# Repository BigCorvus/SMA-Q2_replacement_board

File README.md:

# SMA-Q2_replacement_board

Custom replacement board with an nrf52840 module based on the feather board. It features a https://abracon.com/realtimeclock/AB-RTCMC-32.768kHz-IBO5-S3.pdf RTC with a tiny superca for timekeeping. It will take care of generating the extcomin signal and minute-wise updates of the display. In between the updates the MCU can be turned off completely which can lead to very low  overall power consumption of the watch. That way one can just write Sketches for the nrf52840 without having to engineer low power stuff, so one should have a reliable device capable for everyday use. You have native USB for DFU und other communication via the charging cable which has a USB plug connected to the  four contacts anyway. The accelerometer is a BMA400 and the heart rate sensor based on https://pulsesensor.com sitting on a custom flex PCB connected to an analog input: https://github.com/BigCorvus/PulseSensor-for-SMA-Q2/tree/master

The current version snapfits almost perfectly into the LCD frame. Had to file a corner for a fraction of a millimeter.

The BOM is not quite finished yet because I have not setteled on the final component values, but most of them should be straightforward. Just consult the schematc. 
The dual P-Channel mosfets might be CMLDM8005 TR PBFREE (Digikey 1514-CMLDM8005TRPBFREECT-ND). 
Pushbuttons are LS12T2-T (Digikey 1642-1312-1-ND).
The supercap is Seiko CPH3225A (728-1127-1-ND). 
The RTC is Abracon AB-RTCMC-32.768kHz-IBO5-S3 (535-13301-1-ND). 
The display connectors are 255-3056-1-ND and 255-5667-ND. 
Accelerometer is 828-1081-1-ND (BMA400). 
Schottky diodes are 497-7163-1-ND. 
Flash chip is 1970-1011-1-ND. 
LDO is 296-24059-1-ND. 
The BT module is a Raytac MDBT50Q (1597-1678-ND). 
Watch crystal: 478-5428-1-ND. 
Mosfet for vibrator is DMG1012UW-7DICT-ND.
LED for HR sensor: 1497-1162-1-ND, Opamp: MCP6001T-I/LTCT-ND.
The vibration motor is 8mm in diameter and 2mm high. Can be found on Aliexpress.  
  
Newer version: https://github.com/BigCorvus/SMA-Q2_replacement_board_v2  
Arduino Firmware: https://github.com/BigCorvus/SMA-Q2-nrf52840-dualMode-firmware

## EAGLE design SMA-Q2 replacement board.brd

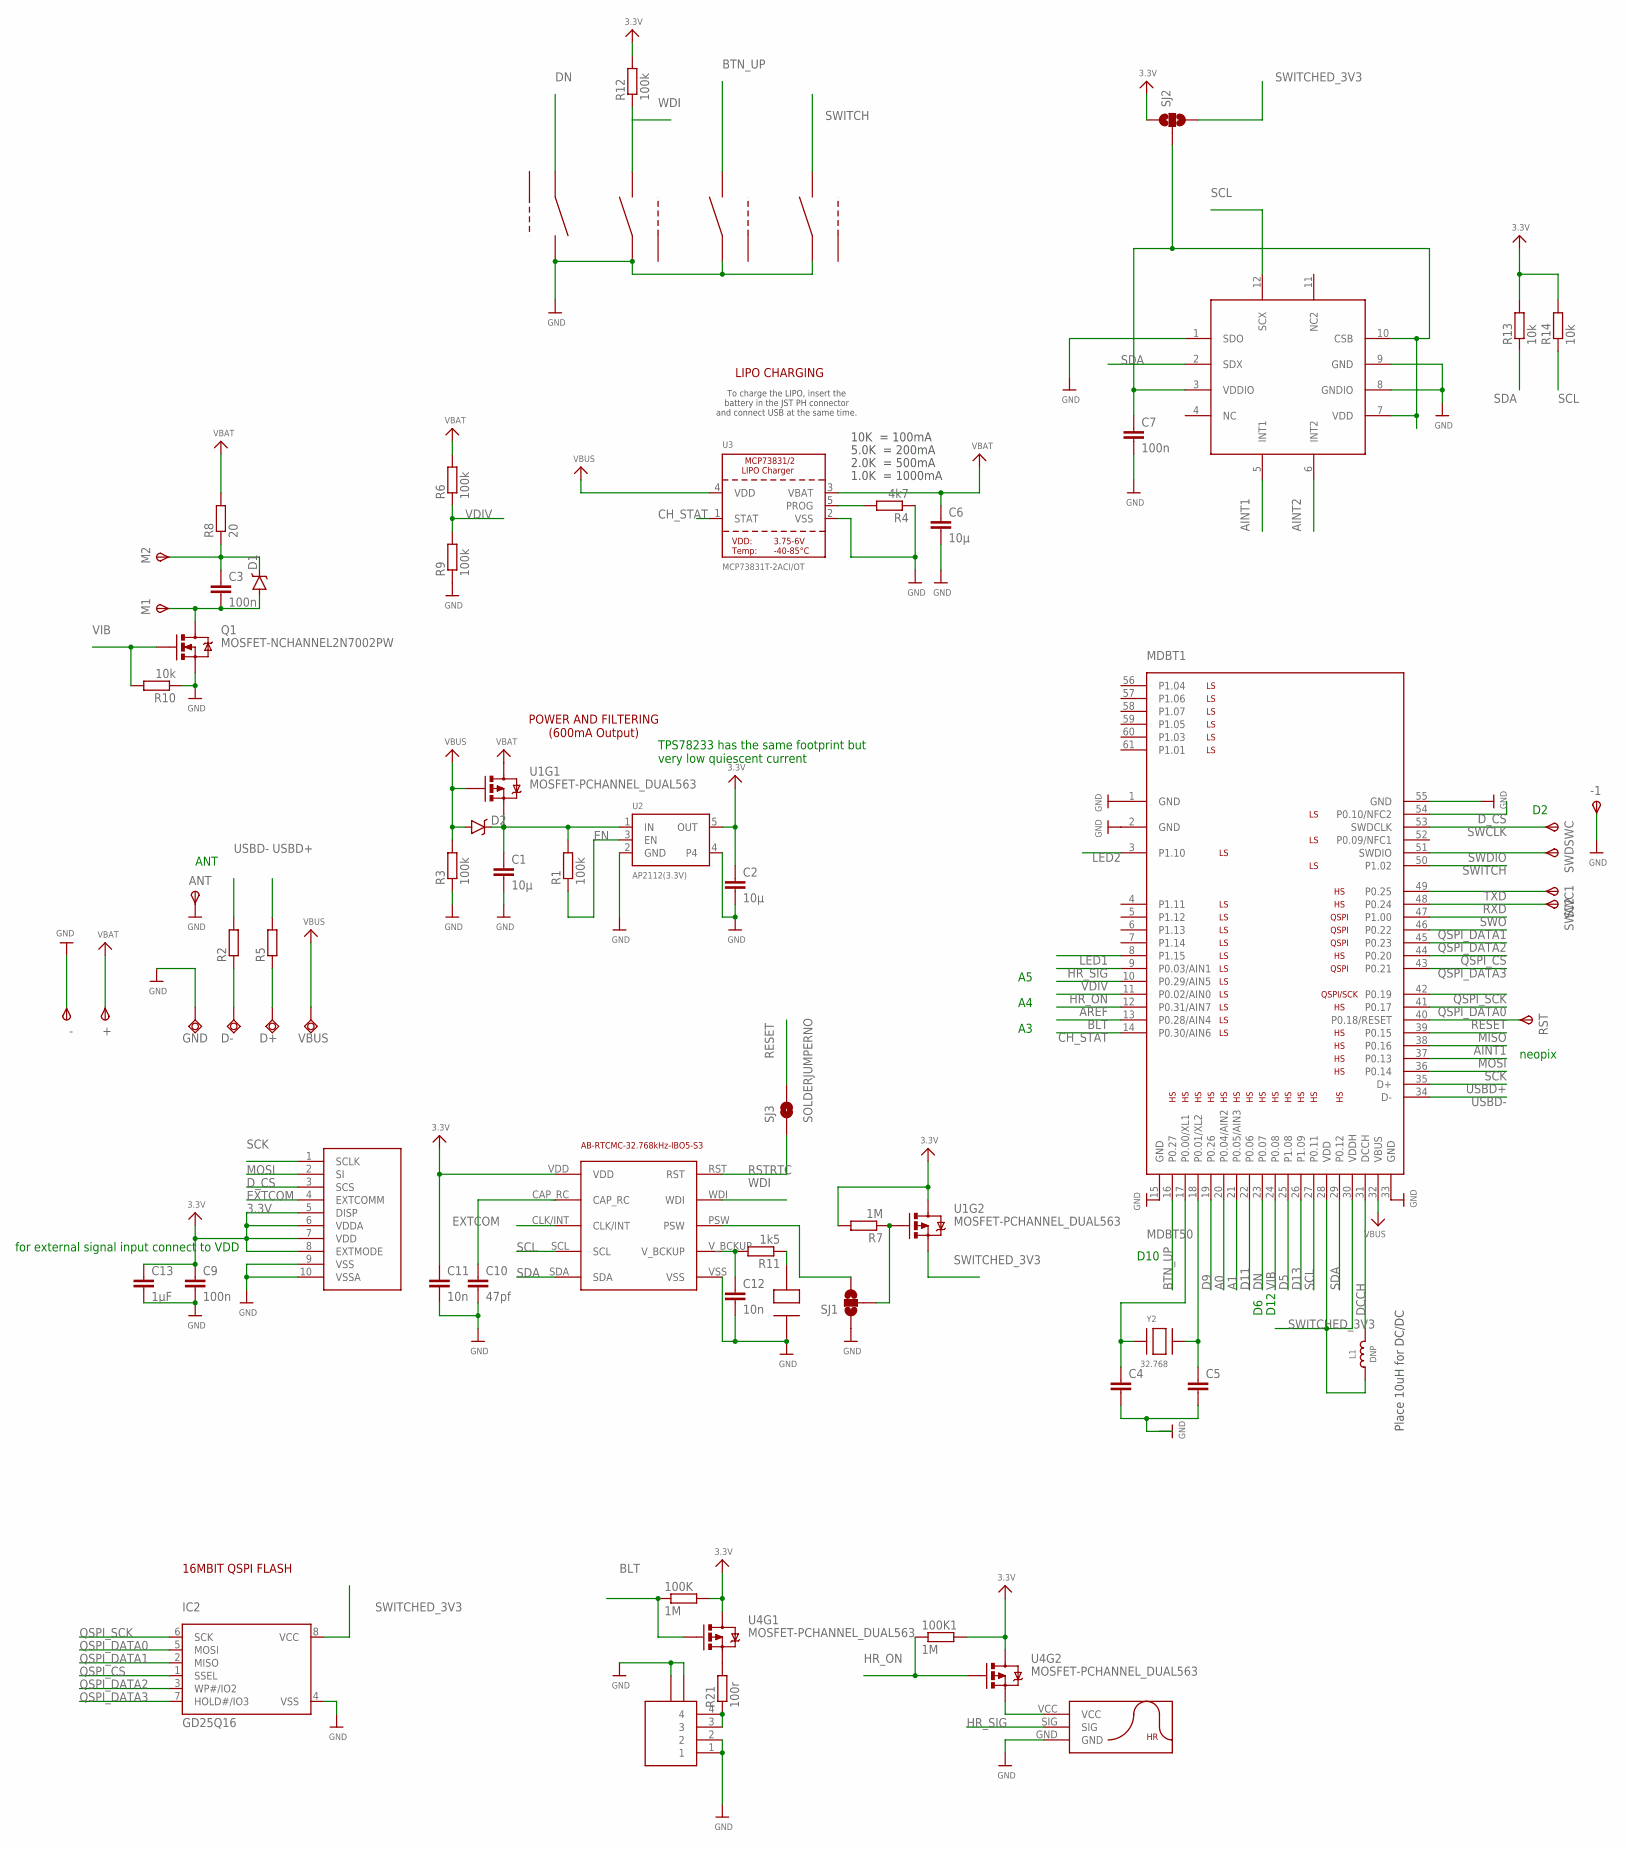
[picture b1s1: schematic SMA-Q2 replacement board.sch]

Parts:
100K, 100K1: 1M; R0402
+: TPSTP09R; TP09R
-, -1: TPSTP09R; TP09R
ANT: TPSTP19SQ; TP19SQ
C1, C2, C6: 10µ; C0603
C3, C7, C9: 100n; C0402
C4, C5: C-EUC0402; C0402
C10: 47pf; C0402
C11, C12: 10n; C0402
C13: 1µF; C0402
D1, D2: BAT20J; SOD-323
D+: TPSQTP20R; TP20R
D-: TPSQTP20R; TP20R
DWN, DWN1, DWN2, DWN3: LS12T2
GND: TPSQTP20R; TP20R
IC2: GD25Q16; USON8
L1: DNP; _0805MP
M1, M2: TPSTP09R; TP09R
MDBT1: MDBT50
Q1: MOSFET-NCHANNEL2N7002PW; SOT323
R1, R3, R6, R9, R12: 100k; R0402
R2, R5: R-EU_R0402; R0402
R4: 4k7; R0402
R7: 1M; R0402
R8: 20; R0402
R10, R13, R14: 10k; R0402
R11: 1k5; R0402
R21: 100r; R0402
RST: TPSTP09R; TP09R
SJ1, SJ2: SOLDERJUMPER_2WAYS; SJ_3
SJ3: SOLDERJUMPERNO; SJ_2S-NO
SWC, SWC1, SWC2: TPSTP09R; TP09R
SWD: TPSTP09R; TP09R
U1, U4: MOSFET-PCHANNEL_DUAL563; SOT563
U2: AP2112(3.3V); SOT23-5
U3: MCP73831T-2ACI/OT; SOT23-5
U$1: AB-RTCMC-32.768KHZ-IBO5-S3
U$2: SHARP_MEM_DISP; Y5BW
U$6: Y5B-4PIN
U$7: BMA400
U$15: CPH3225A
U$45: HR_PADS
VBUS: TPSQTP20R; TP20R
Y2: 32.768; XTAL3215

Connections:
3.3V: 100K.2, 100K1.2, C2.1, C9.1, C11.1, C13.1, R7.2, R12.2, R13.2, R14.2, SJ2.1, U1.D2 (D), U2.5 (OUT), U4.D1 (D), U4.D2 (D), U$1.VDD, U$2.5 (DISP), U$2.6 (VDDA), U$2.7 (VDD), U$2.8 (EXTMODE)
A0: MDBT1.20 (P0.04/AIN2)
A1: MDBT1.21 (P0.05/AIN3)
AINT1: MDBT1.38 (P0.16), U$7.5 (INT1)
AINT2: U$7.6 (INT2)
AREF: MDBT1.12 (P0.31/AIN7)
BLT: 100K.1, MDBT1.13 (P0.28/AIN4), U4.G1 (G)
BTN_UP: DWN2.1, MDBT1.16 (P0.27)
CH_STAT: MDBT1.14 (P0.30/AIN6), U3.1 (STAT)
D5: MDBT1.25 (P1.08)
D9: MDBT1.19 (P0.26)
D11: MDBT1.22 (P0.06)
D13: MDBT1.26 (P1.09)
DCCH: L1.2, MDBT1.31 (DCCH)
DN: DWN.2, MDBT1.23 (P0.07)
D_CS: MDBT1.54 (P0.10/NFC2), U$2.3 (SCS)
EN: R1.1, U2.3 (EN)
EXTCOM: U$1.CLK/INT, U$2.4 (EXTCOMM)
GND: -.TP, -1.TP, ANT.TP, C1.2, C2.2, C4.2, C5.2, C6.2, C7.2, C9.2, C10.2, C11.2, C12.2, C13.2, DWN.1, DWN1.2, DWN2.2, DWN3.2, GND.TP, IC2.4 (VSS), MDBT1.1 (GND), MDBT1.2 (GND), MDBT1.15 (GND), MDBT1.33 (GND), MDBT1.55 (GND), Q1.2 (S), R3.1, R4.1, R9.1, R10.1, SJ1.1, U2.2 (GND), U2.4, U3.2 (VSS), U$1.VSS, U$2.9 (VSS), U$2.10 (VSSA), U$6.1, U$6.2, U$6.H1, U$6.H2, U$7.1 (SDO), U$7.8 (GNDIO), U$7.9 (GND), U$15.-, U$45.GND
HR_ON: 100K1.1, MDBT1.11 (P0.02/AIN0), U4.G2 (G)
HR_SIG: MDBT1.9 (P0.03/AIN1), U$45.SIG
LED1: MDBT1.8 (P1.15)
LED2: MDBT1.3 (P1.10)
MISO: MDBT1.39 (P0.15)
MOSI: MDBT1.37 (P0.13), U$2.2 (SI)
unnamed: R7.1, SJ1.2, U1.G2 (G)
unnamed: C10.1, U$1.CAP_RC
unnamed: D-.TP, R2.1
unnamed: D+.TP, R5.1
unnamed: C7.1, SJ2.2, U$7.3 (VDDIO), U$7.7 (VDD), U$7.10 (CSB)
unnamed: SJ1.3, U$1.PSW
unnamed: C4.1, MDBT1.17 (P0.00/XL1), Y2.P$1
unnamed: C5.1, MDBT1.18 (P0.01/XL2), Y2.P$2
unnamed: R21.1, U$6.3, U$6.4
unnamed: C12.1, R11.2, U$1.V_BCKUP
unnamed: R11.1, U$15.+
unnamed: R4.2, U3.5 (PROG)
unnamed: C3.2, D1.A, M1.TP, Q1.3 (D)
unnamed: C3.1, D1.C, M2.TP, R8.1
unnamed: U4.S2 (S), U$45.VCC
unnamed: R21.2, U4.S1 (S)
QSPI_CS: IC2.1 (SSEL), MDBT1.44 (P0.20)
QSPI_DATA0: IC2.5 (MOSI), MDBT1.41 (P0.17)
QSPI_DATA1: IC2.2 (MISO), MDBT1.46 (P0.22)
QSPI_DATA2: IC2.3 (WP#/IO2), MDBT1.45 (P0.23)
QSPI_DATA3: IC2.7 (HOLD#/IO3), MDBT1.43 (P0.21)
QSPI_SCK: IC2.6 (SCK), MDBT1.42 (P0.19)
RESET: MDBT1.40 (P0.18/RESET), RST.TP, SJ3.2
RSTRTC: SJ3.1, U$1.RST
RXD: MDBT1.48 (P0.24), SWC2.TP
SCK: MDBT1.36 (P0.14), U$2.1 (SCLK)
SCL: MDBT1.27 (P0.11), R14.1, U$1.SCL, U$7.12 (SCX)
SDA: MDBT1.29 (P0.12), R13.1, U$1.SDA, U$7.2 (SDX)
SWCLK: MDBT1.53 (SWDCLK), SWC.TP
SWDIO: MDBT1.51 (SWDIO), SWD.TP
SWITCH: DWN3.1, MDBT1.50 (P1.02)
SWITCHED_3V3: IC2.8 (VCC), L1.1, MDBT1.28 (VDD), MDBT1.30 (VDDH), SJ2.3, U1.S2 (S)
SWO: MDBT1.47 (P1.00)
TXD: MDBT1.49 (P0.25), SWC1.TP
USBD+: MDBT1.35 (D+), R5.2
USBD-: MDBT1.34 (D-), R2.2
VBAT: +.TP, C6.1, R6.2, R8.2, U1.D1 (D), U3.3 (VBAT)
VBUS: D2.A, MDBT1.32 (VBUS), R3.2, U1.G1 (G), U3.4 (VDD), VBUS.TP
VDIV: MDBT1.10 (P0.29/AIN5), R6.1, R9.2
VHI: C1.1, D2.C, R1.2, U1.S1 (S), U2.1 (IN)
VIB: MDBT1.24 (P0.08), Q1.1 (G), R10.2
WDI: DWN1.1, R12.1, U$1.WDI

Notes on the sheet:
Place 10uH for DC/DC
10K = 100mA
5.0K = 200mA
2.0K = 500mA
1.0K = 1000mA
LIPO CHARGING
To charge the LIPO, insert the battery in the JST PH connector and connect USB at the same time.
POWER AND FILTERING (600mA Output)
ANT
TPS78233 has the same footprint but very low quiescent current
16MBIT QSPI FLASH
for external signal input connect to VDD
D10
D12
neopix

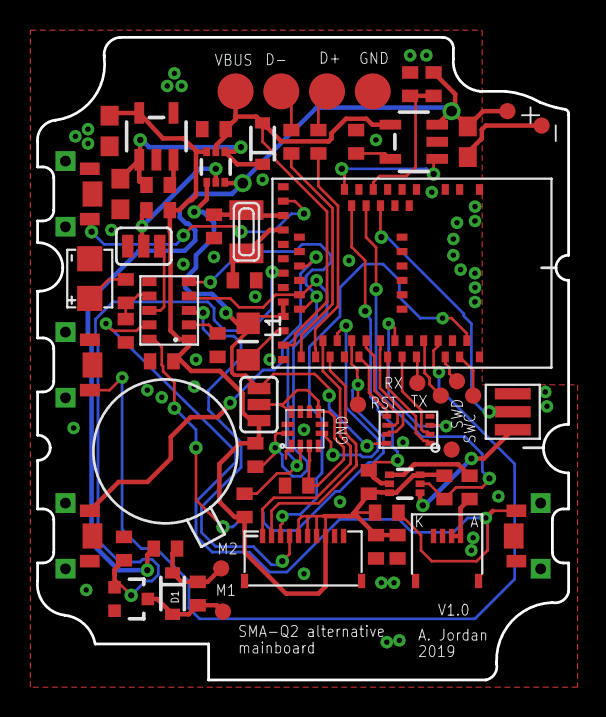
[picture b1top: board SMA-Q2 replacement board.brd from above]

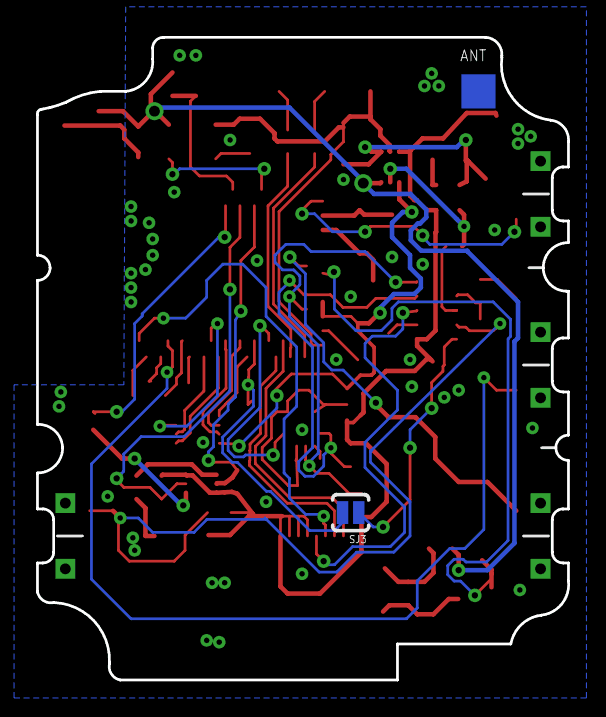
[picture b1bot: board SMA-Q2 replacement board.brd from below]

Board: 2 copper layers, 29.5 x 35.7 mm, 68 parts (2 on the bottom side), 55 nets.

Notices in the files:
parts and their libraries:
microbuilder: This work is placed in the public domain, and may be freely used for commercial and non-commercial work with the following conditions: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
SparkFun-DiscreteSemi: Licensing: Creative Commons ShareAlike 4.0 International - https://creativecommons.org/licenses/by-sa/4.0
